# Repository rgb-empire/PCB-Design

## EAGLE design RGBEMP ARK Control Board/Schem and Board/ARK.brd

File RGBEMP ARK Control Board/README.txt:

DIRECTORY NAME:         Logic Board w Basic Distro
QUANTITY ORDERED:       10 PCBs, individually routed, of one single design
BASIC SPECIFICATIONS:   2-layers, XX" x XX", 12 mil trace/space, 20 mil minimum plated hole
//FABRICATION SPEED:      Shipment within 5 business days after placement of order

+-+-+-+-+-+-+-+-+-+-+-+-+-+-+-+-+-+-+-+-+-+-+-+-+-+-+-+-+-+-+-+-+-+-+-

1)  Technical Contact Info:

     Mr. David Cain
     d.cain2740@gmail.com
     (xxx)123-4567    Cell
	
2)  File Names

     .drd  Excellon Drill Data  
     .gtl  Component Side (Top)  
     .ly2  Layer under component Side (Layer 2)  
     .ly3  Layer above solder side (Layer 3)  
     .gbl  Solder side (Bottom)  
     .gto  Sikscreen, top side  
     .gts  solder stop, top side  
     .gbs  solder stop, bottom side  
     .gtp  Solder paste, top side  
     .gm1  Mechanical outline  

3)  Non-Gerber Specs  

     Copper weight:  1oz outer layers, 0.5oz inner layers  
     Solder Mask Color: green  
     Overlay Color: white  

4)  Shipping Information:

     Ship via UPS or FedEx 3-day delivery to:

     Mr. LaserAlex  
     123 Yellowbrick Road  
     Emerald City, OZ 12345

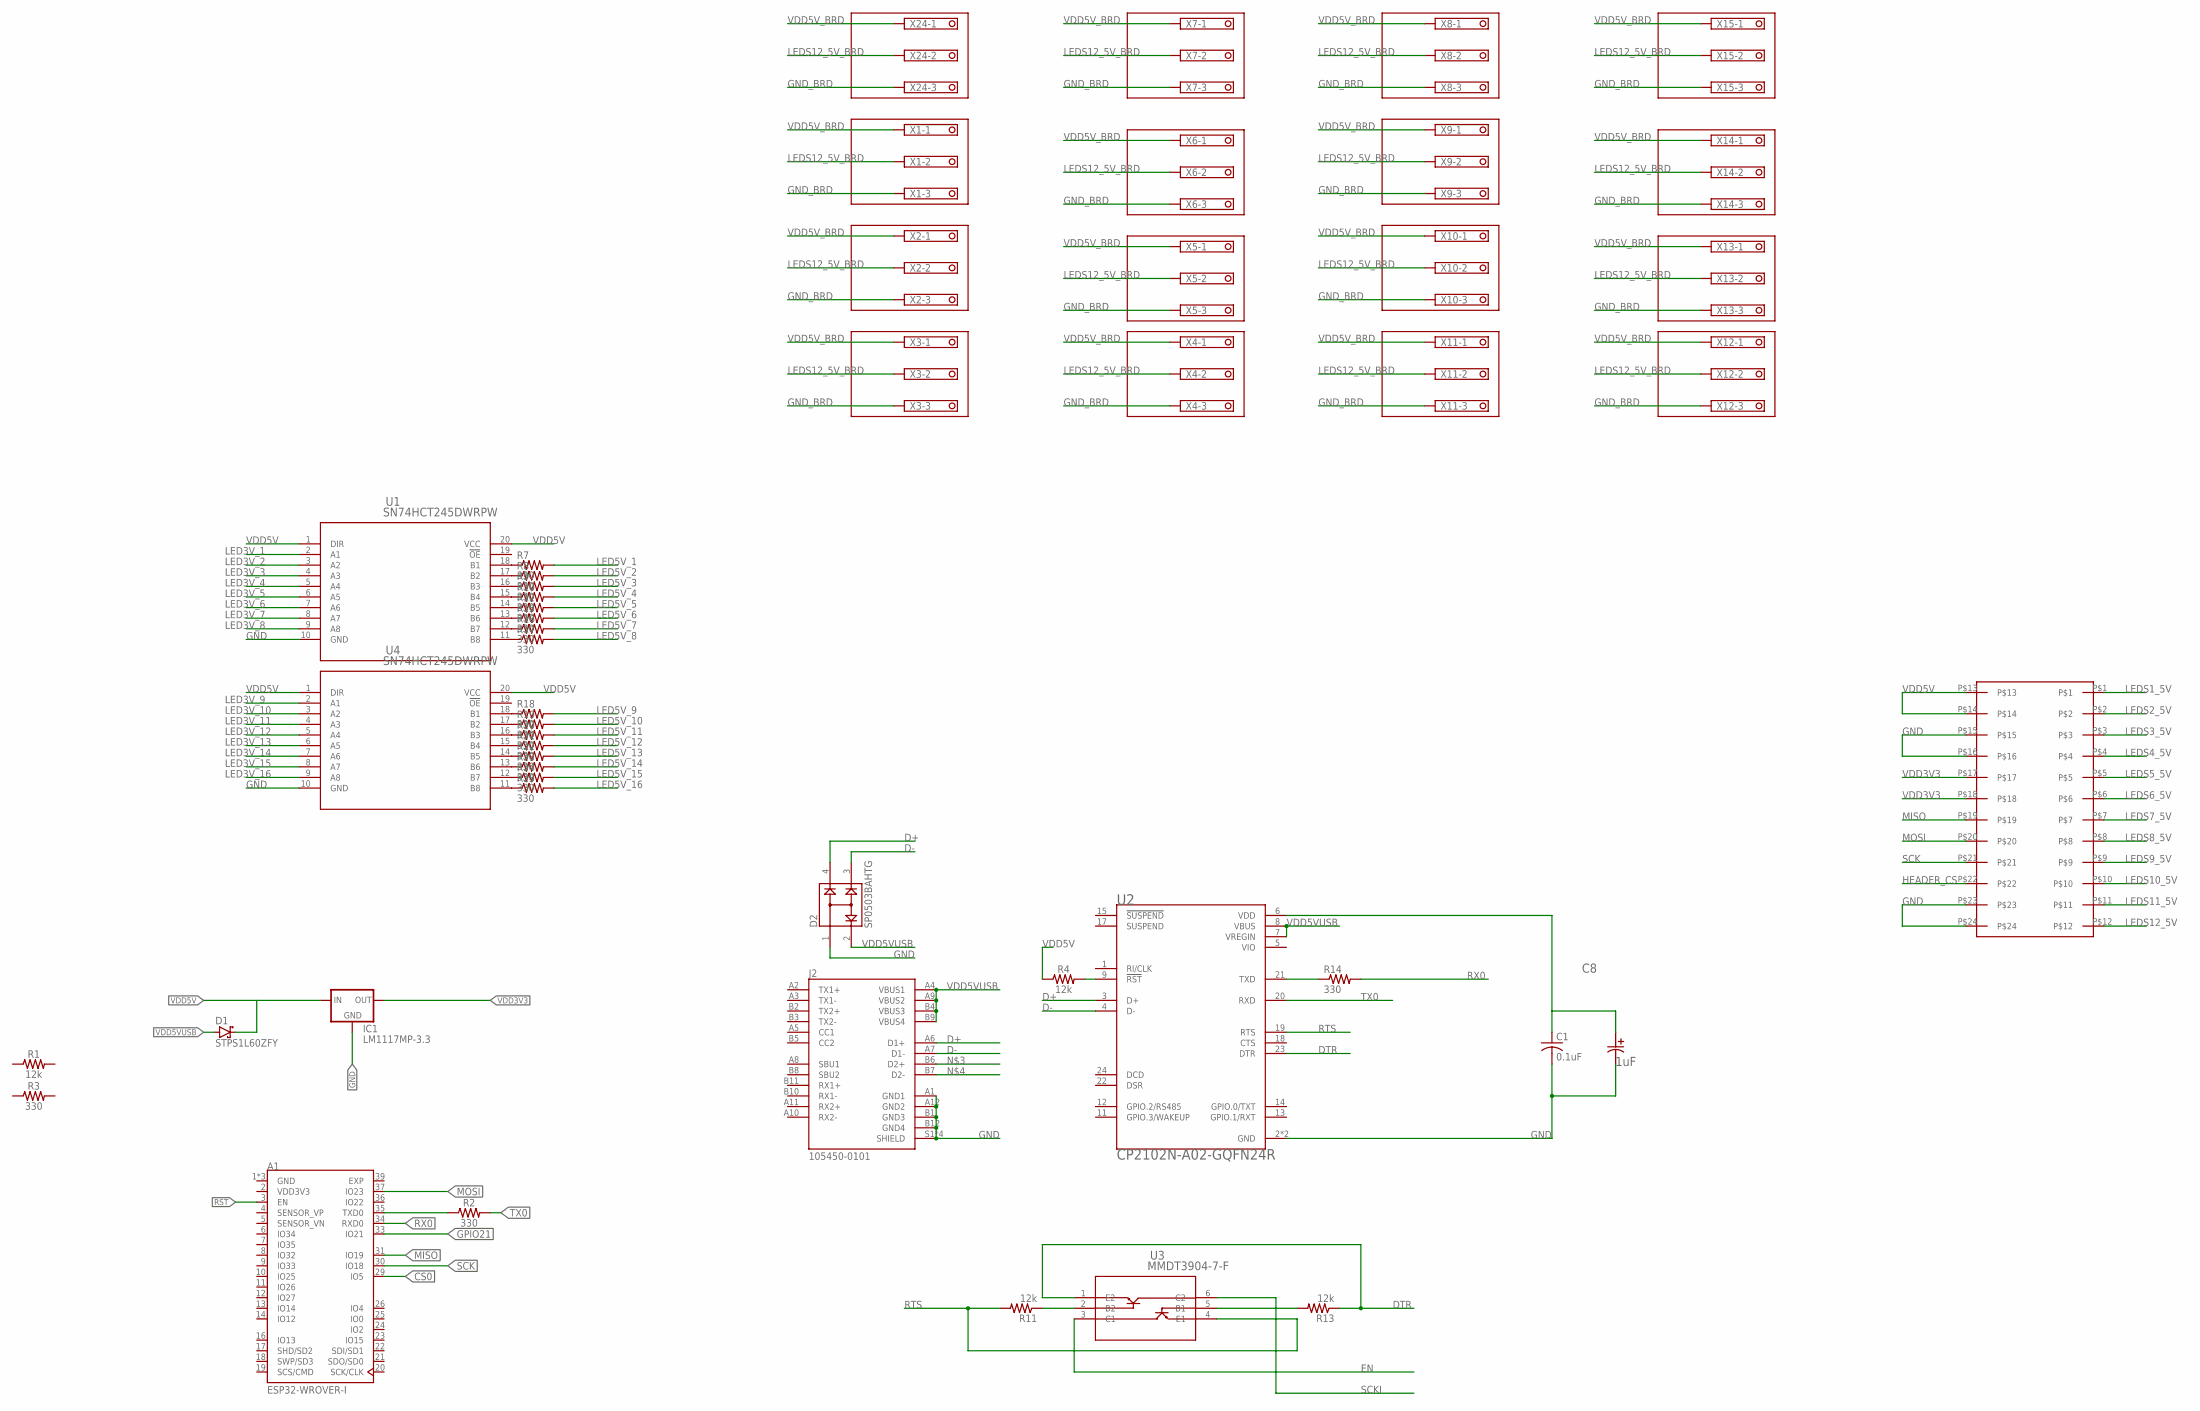
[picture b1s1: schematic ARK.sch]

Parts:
A1: ESP32-WROVER-I; XCVR_ESP32-WROVER-I
C1: 0.1uF; C0402
C8: 1uF; CAP_EEFC_B
D1: STPS1L60ZFY; SOD-123
D2: SP0503BAHTG; SOT143
IC1: LM1117MP-3.3; SOT223
J2: 105450-0101; MOLEX_105450-0101
R1, R4: 12k; 0603
R2, R3: 330; 0603
R7, R8, R9, R10, R12, R14, R15, R16, R17, R18, R19, R20, R21, R22, R23, R24, R25: 330; RES_0603
R11, R13: 12k; RES_0603
U1, U4: SN74HCT245DWRPW; PW
U2: CP2102N-A02-GQFN24R; SILABS_CP2102N-A02-GQFN24R
U3: MMDT3904-7-F; SOT-363
U$9: MY_HEADER
X1, X2, X3, X4, X5, X6, X7, X8, X9, X10, X11, X12, X13, X14, X15, X24: TERMINAL-BLOCK-3.5MM-3-PIN-LONG-PAD; TERMINAL-BLOCK-3-PIN-3.5MM-LONG-PAD

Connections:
CS0: A1.29 (IO5)
D+: D2.4, J2.A6 (D1+), U2.3 (D+)
D-: D2.3, J2.A7 (D1-), U2.4 (D-)
DTR: R13.1, U2.23 (DTR), U3.1 (E2)
EN: U3.3 (C1)
EXP: A1.39 (EXP)
GND: A1.1 (GND), A1.15 (GND), A1.38 (GND), C1.2, C8.2, D2.1, IC1.1 (GND), J2.A1 (GND1), J2.A12 (GND2), J2.B1 (GND3), J2.B12 (GND4), J2.S1 (SHIELD), J2.S2 (SHIELD), J2.S3 (SHIELD), J2.S4 (SHIELD), U1.10 (GND), U2.2 (GND), U2.25 (GND), U4.10 (GND), U$9.P$15, U$9.P$16, U$9.P$23, U$9.P$24
GND_BRD: X1.3, X2.3, X3.3, X4.3, X5.3, X6.3, X7.3, X8.3, X9.3, X10.3, X11.3, X12.3, X13.3, X14.3, X15.3, X24.3
GPIO21: A1.33 (IO21)
HEADER_CS: U$9.P$22
LED3V_1: U1.2 (A1)
LED3V_2: U1.3 (A2)
LED3V_3: U1.4 (A3)
LED3V_4: U1.5 (A4)
LED3V_5: U1.6 (A5)
LED3V_6: U1.7 (A6)
LED3V_7: U1.8 (A7)
LED3V_8: U1.9 (A8)
LED3V_9: U4.2 (A1)
LED3V_10: U4.3 (A2)
LED3V_11: U4.4 (A3)
LED3V_12: U4.5 (A4)
LED3V_13: U4.6 (A5)
LED3V_14: U4.7 (A6)
LED3V_15: U4.8 (A7)
LED3V_16: U4.9 (A8)
LED5V_1: R7.2
LED5V_2: R8.2
LED5V_3: R9.2
LED5V_4: R10.2
LED5V_5: R12.2
LED5V_6: R15.2
LED5V_7: R16.2
LED5V_8: R17.2
LED5V_9: R18.2
LED5V_10: R19.2
LED5V_11: R20.2
LED5V_12: R21.2
LED5V_13: R22.2
LED5V_14: R23.2
LED5V_15: R24.2
LED5V_16: R25.2
LEDS1_5V: U$9.P$1
LEDS2_5V: U$9.P$2
LEDS3_5V: U$9.P$3
LEDS4_5V: U$9.P$4
LEDS5_5V: U$9.P$5
LEDS6_5V: U$9.P$6
LEDS7_5V: U$9.P$7
LEDS8_5V: U$9.P$8
LEDS9_5V: U$9.P$9
LEDS10_5V: U$9.P$10
LEDS11_5V: U$9.P$11
LEDS12_5V: U$9.P$12
LEDS12_5V_BRD: X1.2, X2.2, X3.2, X4.2, X5.2, X6.2, X7.2, X8.2, X9.2, X10.2, X11.2, X12.2, X13.2, X14.2, X15.2, X24.2
MISO: A1.31 (IO19), U$9.P$19
MOSI: A1.37 (IO23), U$9.P$20
unnamed: A1.35 (TXD0), R2.1
unnamed: C1.1, C8.1, U2.6 (VDD)
unnamed: R4.2, U2.9 (!RST)
unnamed: R11.1, U3.2 (B2)
unnamed: R13.2, U3.5 (B1)
unnamed: R7.1, U1.18 (B1)
unnamed: R8.1, U1.17 (B2)
unnamed: R9.1, U1.16 (B3)
unnamed: R10.1, U1.15 (B4)
unnamed: R12.1, U1.14 (B5)
unnamed: R15.1, U1.13 (B6)
unnamed: R16.1, U1.12 (B7)
unnamed: R14.1, U2.21 (TXD)
unnamed: R17.1, U1.11 (B8)
unnamed: R18.1, U4.18 (B1)
unnamed: R19.1, U4.17 (B2)
unnamed: R20.1, U4.16 (B3)
unnamed: R21.1, U4.15 (B4)
unnamed: R22.1, U4.14 (B5)
unnamed: R23.1, U4.13 (B6)
unnamed: R24.1, U4.12 (B7)
unnamed: R25.1, U4.11 (B8)
RST: A1.3 (EN)
RTS: R11.2, U2.19 (RTS), U3.4 (E1)
RX0: A1.34 (RXD0), R14.2
SCK: A1.30 (IO18), U$9.P$21
SCKI: U3.6 (C2)
TX0: R2.2, U2.20 (RXD)
VDD3V3: A1.2 (VDD3V3), IC1.2 (OUT), IC1.4 (OUT), U$9.P$17, U$9.P$18
VDD5V: IC1.3 (IN), R4.1, U1.1 (DIR), U1.20 (VCC), U4.1 (DIR), U4.20 (VCC), U$9.P$13, U$9.P$14
VDD5VUSB: D1.A, D2.2, J2.A4 (VBUS1), J2.A9 (VBUS2), J2.B4 (VBUS3), J2.B9 (VBUS4), U2.7 (VREGIN), U2.8 (VBUS)
VDD5V_BRD: X1.1, X2.1, X3.1, X4.1, X5.1, X6.1, X7.1, X8.1, X9.1, X10.1, X11.1, X12.1, X13.1, X14.1, X15.1, X24.1

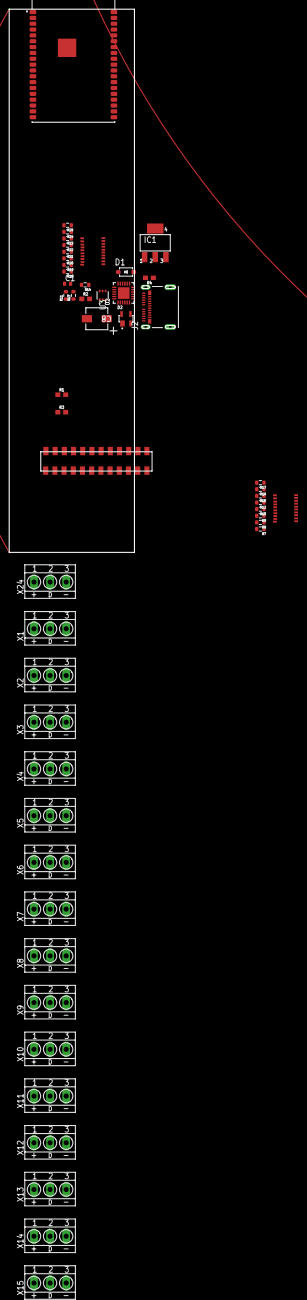
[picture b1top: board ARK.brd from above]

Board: 2 copper layers, 36.1 x 118.1 mm, 51 parts (0 on the bottom side), 38 nets.

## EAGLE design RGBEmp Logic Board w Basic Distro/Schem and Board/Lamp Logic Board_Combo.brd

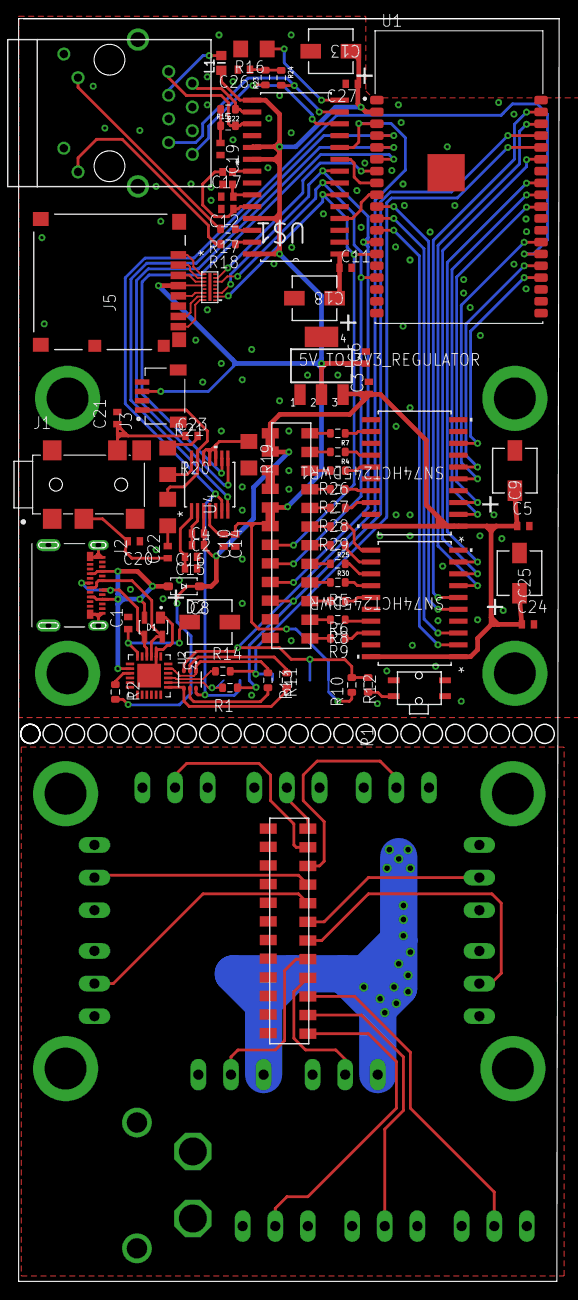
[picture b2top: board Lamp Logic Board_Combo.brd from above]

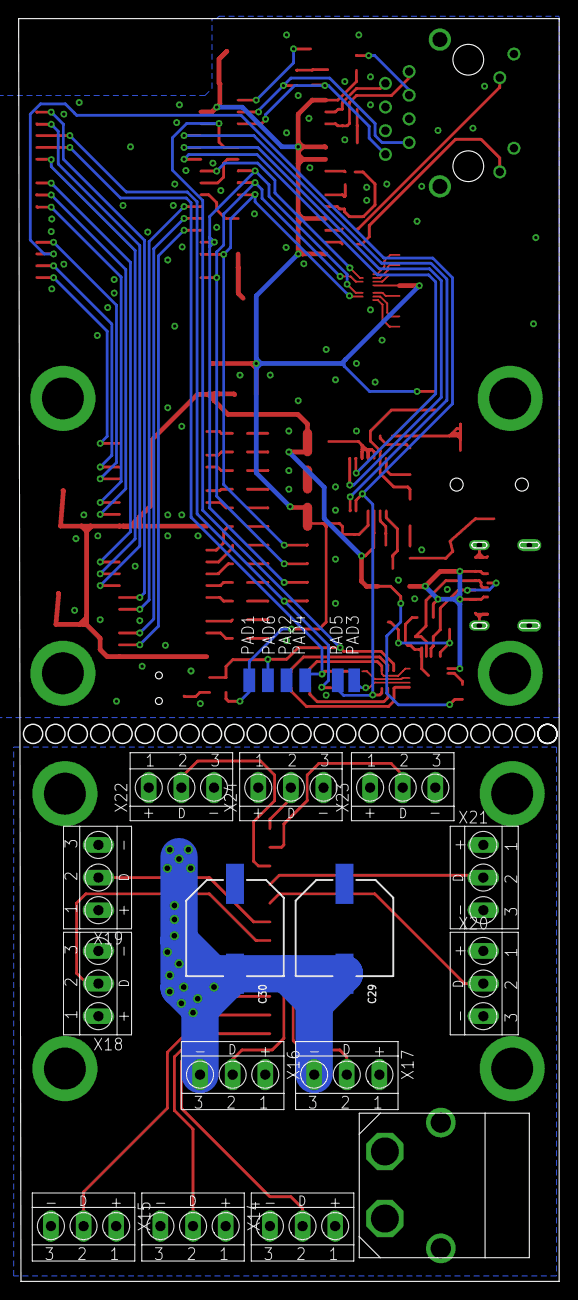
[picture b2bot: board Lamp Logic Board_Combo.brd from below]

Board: 2 copper layers, 58.0 x 135.5 mm, 102 parts (22 on the bottom side), 109 nets.

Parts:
5V_TO_3V3_REGULATOR: SOT223
C1, C4, C5, C14, C16, C19, C20, C21, C24, C26: 0.1uF; C0402
C2, C3, C6, C10, C15, C22, C23, C27: 1uF; C0402
C8, C9, C25: 1uF; CAP_EEFC_B
C11: 10uF; C0402
C12, C17: 6pF; C0402
C13, C18: 100uF; CAP_EEFC_B
C29, C30: 1000uF; CSV-G
D1: SP0503BAHTG; SOT143
D2: STPS1L60ZFY; SOD-123
J1: SJ2-35894D-SMT-TR; CUI_SJ2-35894D-SMT-TR
J2: 105450-0101; MOLEX_105450-0101
J3: SM04B-SRSS-TB(LF)(SN); JST_SM04B-SRSS-TB(LF)(SN)
J5: LLC; CON00218_8
L1: EXC3BP; L0603
P1: RB1-125BAG1A; WIZNET_RB1-125BAG1A
PAD1: VCC; SMD1,27-2,54
PAD2: GND; SMD1,27-2,54
PAD3: TX; SMD1,27-2,54
PAD4: RX; SMD1,27-2,54
PAD5: DTR; SMD1,27-2,54
PAD6: RTS; SMD1,27-2,54
R1, R4, R5, R6, R7, R8, R9, R10, R14, R15, R17, R18, R22, R23, R24, R25, R26, R27, R28, R29, R30: 330; RES_0603
R2, R11, R12, R13: 12k; RES_0603
R16: 2.32k; R1206
R19: 10k; R1206
R20, R21: 75; R1206
SN74HCT245DWR, SN74HCT245DWR1: SN74HCT245DWR; DW20
U1: ESP32-WROVER-IB; XCVR_ESP32-WROVER-I
U2: CP2102N-A02-GQFN24R; SILABS_CP2102N-A02-GQFN24R
U3: MMDT3904-7-F; SOT-363
U4: PCM1808PWR; PW14
U$1: ENC28J60/SO; SOIC127P1034X264-28N
U$2: CM1624-08DE
U$3: ECS-250-10-37B-CTN-TR
U$4, U$5, U$6, U$8: QUICKFIT_RISER_THING
U$7: TL1014BF160QG
U$9, U$14: MY_HEADER
U$13,U$14: POWERBOARD_TEMPLATEPOWERBOARD_TEMPLATE; 4,PIECE
U$15: XT60
X13, X14, X15, X16, X17, X18, X19, X20, X21, X22, X23, X24: TERMINAL-BLOCK-3.5MM-3-PIN-LONG-PAD; TERMINAL-BLOCK-3-PIN-3.5MM-LONG-PAD

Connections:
BCK: U1.5, U4.8
CT: L1.2, P1.R3
D+: D1.4, J2.A6, J2.B6, U2.3
D-: D1.3, J2.A7, J2.B7, U2.4
DOUT: U1.6, U4.9
DTR: R13.1, U2.23, U3.1
EN: PAD6.1, R10.1, R12.1, U1.3, U3.3, U$1.10
ETHER_CS: U1.8, U$1.9
ETHER_INT: U1.9, U$1.4
GND: 5V_TO_3V3_REGULATOR.1, C1.2, C3.2, C5.2, C6.2, C8.2, C9.2, C10.2, C11.2, C12.2, C13.2, C14.2, C15.1, C16.1, C17.2, C18.2, C19.2, C20.2, C21.2, C24.2, C25.2, C26.2, C27.2, D1.1, J1.4, J2.A1, J2.A12, J2.B1, J2.B12, J2.S1, J2.S2, J2.S3, J2.S4, J3.4, J3.S1, J3.S2, J5.6, J5.9, J5.10, J5.11, J5.13, J5.14, P1.L2, P1.L4, PAD2.1, R16.2, R19.2, SN74HCT245DWR.10, SN74HCT245DWR.19, SN74HCT245DWR1.10, SN74HCT245DWR1.19, U1.1, U1.15, U1.38, U1.39, U2.2, U2.25, U4.5, U$1.2, U$1.11, U$1.18, U$1.21, U$1.22, U$3.2, U$3.4, U$4.P$1, U$5.P$1, U$6.P$1, U$7.P$1, U$8.P$1, U$9.P$15, U$9.P$16, U$9.P$23, U$9.P$24
GND_BRD: C29.-, C30.-, U$13,U$14.P$1, U$13,U$14.P$2, U$13,U$14.P$3, U$13,U$14.P$4, U$14.P$13, U$14.P$14, U$14.P$21, U$14.P$22, U$15.-, U$15.-_HOLE, X13.3, X14.3, X15.3, X16.3, X17.3, X18.3, X19.3, X20.3, X21.3, X22.3, X23.3, X24.3
HEADER_CS: R1.1, U1.35, U$9.P$22
LEDA: P1.L1, R18.2
LEDB: P1.L3, R17.2
LEDS1_3V3: SN74HCT245DWR1.8, U1.23
LEDS1_5V: R7.2, U$9.P$1
LEDS1_5V_BRD: U$14.P$12, X13.2
LEDS2_3V3: SN74HCT245DWR1.6, U1.24
LEDS2_5V: R4.2, U$9.P$2
LEDS2_5V_BRD: U$14.P$11, X14.2
LEDS3_3V3: SN74HCT245DWR1.5, U1.26
LEDS3_5V: R26.2, U$9.P$3
LEDS3_5V_BRD: U$14.P$10, X15.2
LEDS4_3V3: SN74HCT245DWR1.3, U1.29
LEDS4_5V: R27.2, U$9.P$4
LEDS4_5V_BRD: U$14.P$9, X16.2
LEDS5_3V3: SN74HCT245DWR1.2, U1.30
LEDS5_5V: R28.2, U$9.P$5
LEDS5_5V_BRD: U$14.P$8, X17.2
LEDS6_3V3: SN74HCT245DWR.9, U1.31
LEDS6_5V: R29.2, U$9.P$6
LEDS6_5V_BRD: U$14.P$7, X18.2
LEDS7_3V3: SN74HCT245DWR.8, U1.33
LEDS7_5V: R25.2, U$9.P$7
LEDS7_5V_BRD: U$14.P$6, X19.2
LEDS8_3V3: SN74HCT245DWR.7, U1.36
LEDS8_5V: R30.2, U$9.P$8
LEDS8_5V_BRD: U$14.P$5, X20.2
LEDS9_3V3: SN74HCT245DWR.6, U1.37
LEDS9_5V: R5.2, U$9.P$9
LEDS9_5V_BRD: U$14.P$4, X21.2
LEDS10_3V3: SN74HCT245DWR.5, U1.10
LEDS10_5V: R6.2, U$9.P$10
LEDS10_5V_BRD: U$14.P$3, X22.2
LEDS11_3V3: SN74HCT245DWR.3, U1.11
LEDS11_5V: R8.2, U$9.P$11
LEDS11_5V_BRD: U$14.P$2, X23.2
LEDS12_3V3: SN74HCT245DWR.2, U1.12
LEDS12_5V: R9.2, U$9.P$12
LEDS12_5V_BRD: U$14.P$1, X24.2
LEFT_CHANNEL: R21.2, U4.14
LRCK: U1.4, U4.7
MISO: U1.14, U$1.6, U$2.SDDATA0, U$9.P$19
MOSI: U1.16, U$1.7, U$2.SDCMD, U$9.P$20
unnamed: R9.1, SN74HCT245DWR.18
unnamed: C2.1, C4.1, U4.2
unnamed: C20.1, C22.1, J1.3
unnamed: C21.1, C23.1, J1.2
unnamed: C1.1, C8.1, U2.6
unnamed: R7.1, SN74HCT245DWR1.12
unnamed: R11.1, U3.2
unnamed: R13.2, U3.5
unnamed: R10.2, U$7.P$3
unnamed: R28.1, SN74HCT245DWR1.18
unnamed: R6.1, SN74HCT245DWR.15
unnamed: R5.1, SN74HCT245DWR.14
unnamed: R27.1, SN74HCT245DWR1.17
unnamed: R8.1, SN74HCT245DWR.17
unnamed: R26.1, SN74HCT245DWR1.15
unnamed: C22.2, R20.1
unnamed: C15.2, C16.2, U4.1
unnamed: R14.1, U2.21
unnamed: C11.1, C18.1, U$1.1
unnamed: R16.1, U$1.14
unnamed: C12.1, U$1.24, U$3.1
unnamed: C17.1, U$1.23, U$3.3
unnamed: R17.1, U$1.26
unnamed: C23.2, R21.1
unnamed: R18.1, U$1.27
unnamed: R29.1, SN74HCT245DWR.11
unnamed: R4.1, SN74HCT245DWR1.14
unnamed: R2.1, U2.9
unnamed: R19.1, U4.10, U4.11, U4.12
unnamed: C26.1, R23.2, R24.1
unnamed: C19.1, R15.1, R22.2
unnamed: R30.1, SN74HCT245DWR.13
unnamed: R25.1, SN74HCT245DWR.12
RIGHT_CHANNEL: J3.1, R20.2, U4.13
RTS: R11.2, U2.19, U3.4
RX0: PAD4.1, R14.2, U1.34
SCK: U1.13, U$1.8, U$2.SDCLK, U$9.P$21
SCKI: PAD5.1, U1.25, U3.6, U4.6
SD_CMD: J5.3, U$2.CMD
SD_CS: U1.7, U$2.SDDATA3
SD_D0: J5.7, U$2.DATA0
SD_D1: J5.8, U$2.DATA1
SD_D2: J5.1, U$2.DATA2
SD_D3: J5.2, U$2.DATA3
SD_SCK: J5.5, U$2.CLK
TPIN+: P1.R7, R24.2, U$1.13
TPIN-: P1.R8, R23.1, U$1.12
TPOUT+: P1.R1, R15.2, U$1.17
TPOUT-: P1.R2, R22.1, U$1.16
TX_CONTROLLER: PAD3.1, R1.2, U2.20
VDD3V3: 5V_TO_3V3_REGULATOR.2, 5V_TO_3V3_REGULATOR.4, C6.1, C10.1, C13.1, C14.1, C27.1, J3.3, J5.4, L1.1, PAD1.1, R12.2, U1.2, U4.4, U$1.15, U$1.19, U$1.20, U$1.25, U$1.28, U$2.VCC, U$9.P$17, U$9.P$18
VDD3V3_BRD: U$14.P$19, U$14.P$20
VDD5V: 5V_TO_3V3_REGULATOR.3, C2.2, C3.1, C4.2, C5.1, C9.1, C24.1, C25.1, D2.C, R2.2, SN74HCT245DWR.1, SN74HCT245DWR.20, SN74HCT245DWR1.1, SN74HCT245DWR1.20, U4.3, U$9.P$13, U$9.P$14
VDD5VUSB: D1.2, D2.A, J2.A4, J2.A9, J2.B4, J2.B9, U2.8
VDD5V_BRD: C29.+, C30.+, U$14.P$23, U$14.P$24, U$15.+, U$15.+_HOLE, X13.1, X14.1, X15.1, X16.1, X17.1, X18.1, X19.1, X20.1, X21.1, X22.1, X23.1, X24.1

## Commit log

2020-02-09 did some things

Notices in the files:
parts and their libraries:
lm1117: (c) 2014 Samuel Lourenço
SparkFun-Resistors: Licensing: Creative Commons ShareAlike 4.0 International - https://creativecommons.org/licenses/by-sa/4.0
rc-master-smd: Copyright (C) 2007, Bob Starr
